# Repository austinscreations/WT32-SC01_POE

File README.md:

# WT32-SC01_POE

2023-06-28:

New sheild has been designed that is more universal. the deisgn is much smaller. uses a single 1.25mm jst conenctor to connect to the wt32-sc01 PLUS display.
adapter has been built for the WT32-S3-86s (replaces the 86v) 4" display. adapter in the works to support the orginal display as well

2022-06-23: renamed the repo as this project has evolved

There are now two shields designed for the wt32-sc01 display.
- one offers Ethernet + 802.1af POE
- second offers passive 12-24v POE + a 2.1mm jack

the thought with a passive board is that it's smaller allowing for more compact case designs to be built. and if you prefer to use 802.1af POE with the 2.1mm jack you can very eaily use a standard POE injector that normally cost about $6 from aliexpress to gain such functionality. with teh apssive baord however you are limited to using wifi.

both shields also equipped with qwiic connector for easy i2c support

designed for the use case of using the panel for homeautomation, code and gui in progress.

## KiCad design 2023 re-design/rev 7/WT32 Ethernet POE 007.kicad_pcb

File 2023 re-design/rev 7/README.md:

latest version of the WT32 Ethernet POE
works directly on the WT32-SC01 Plus, and adapters will be availble for the orginal Wt32 screen and the square 86s/86v screen

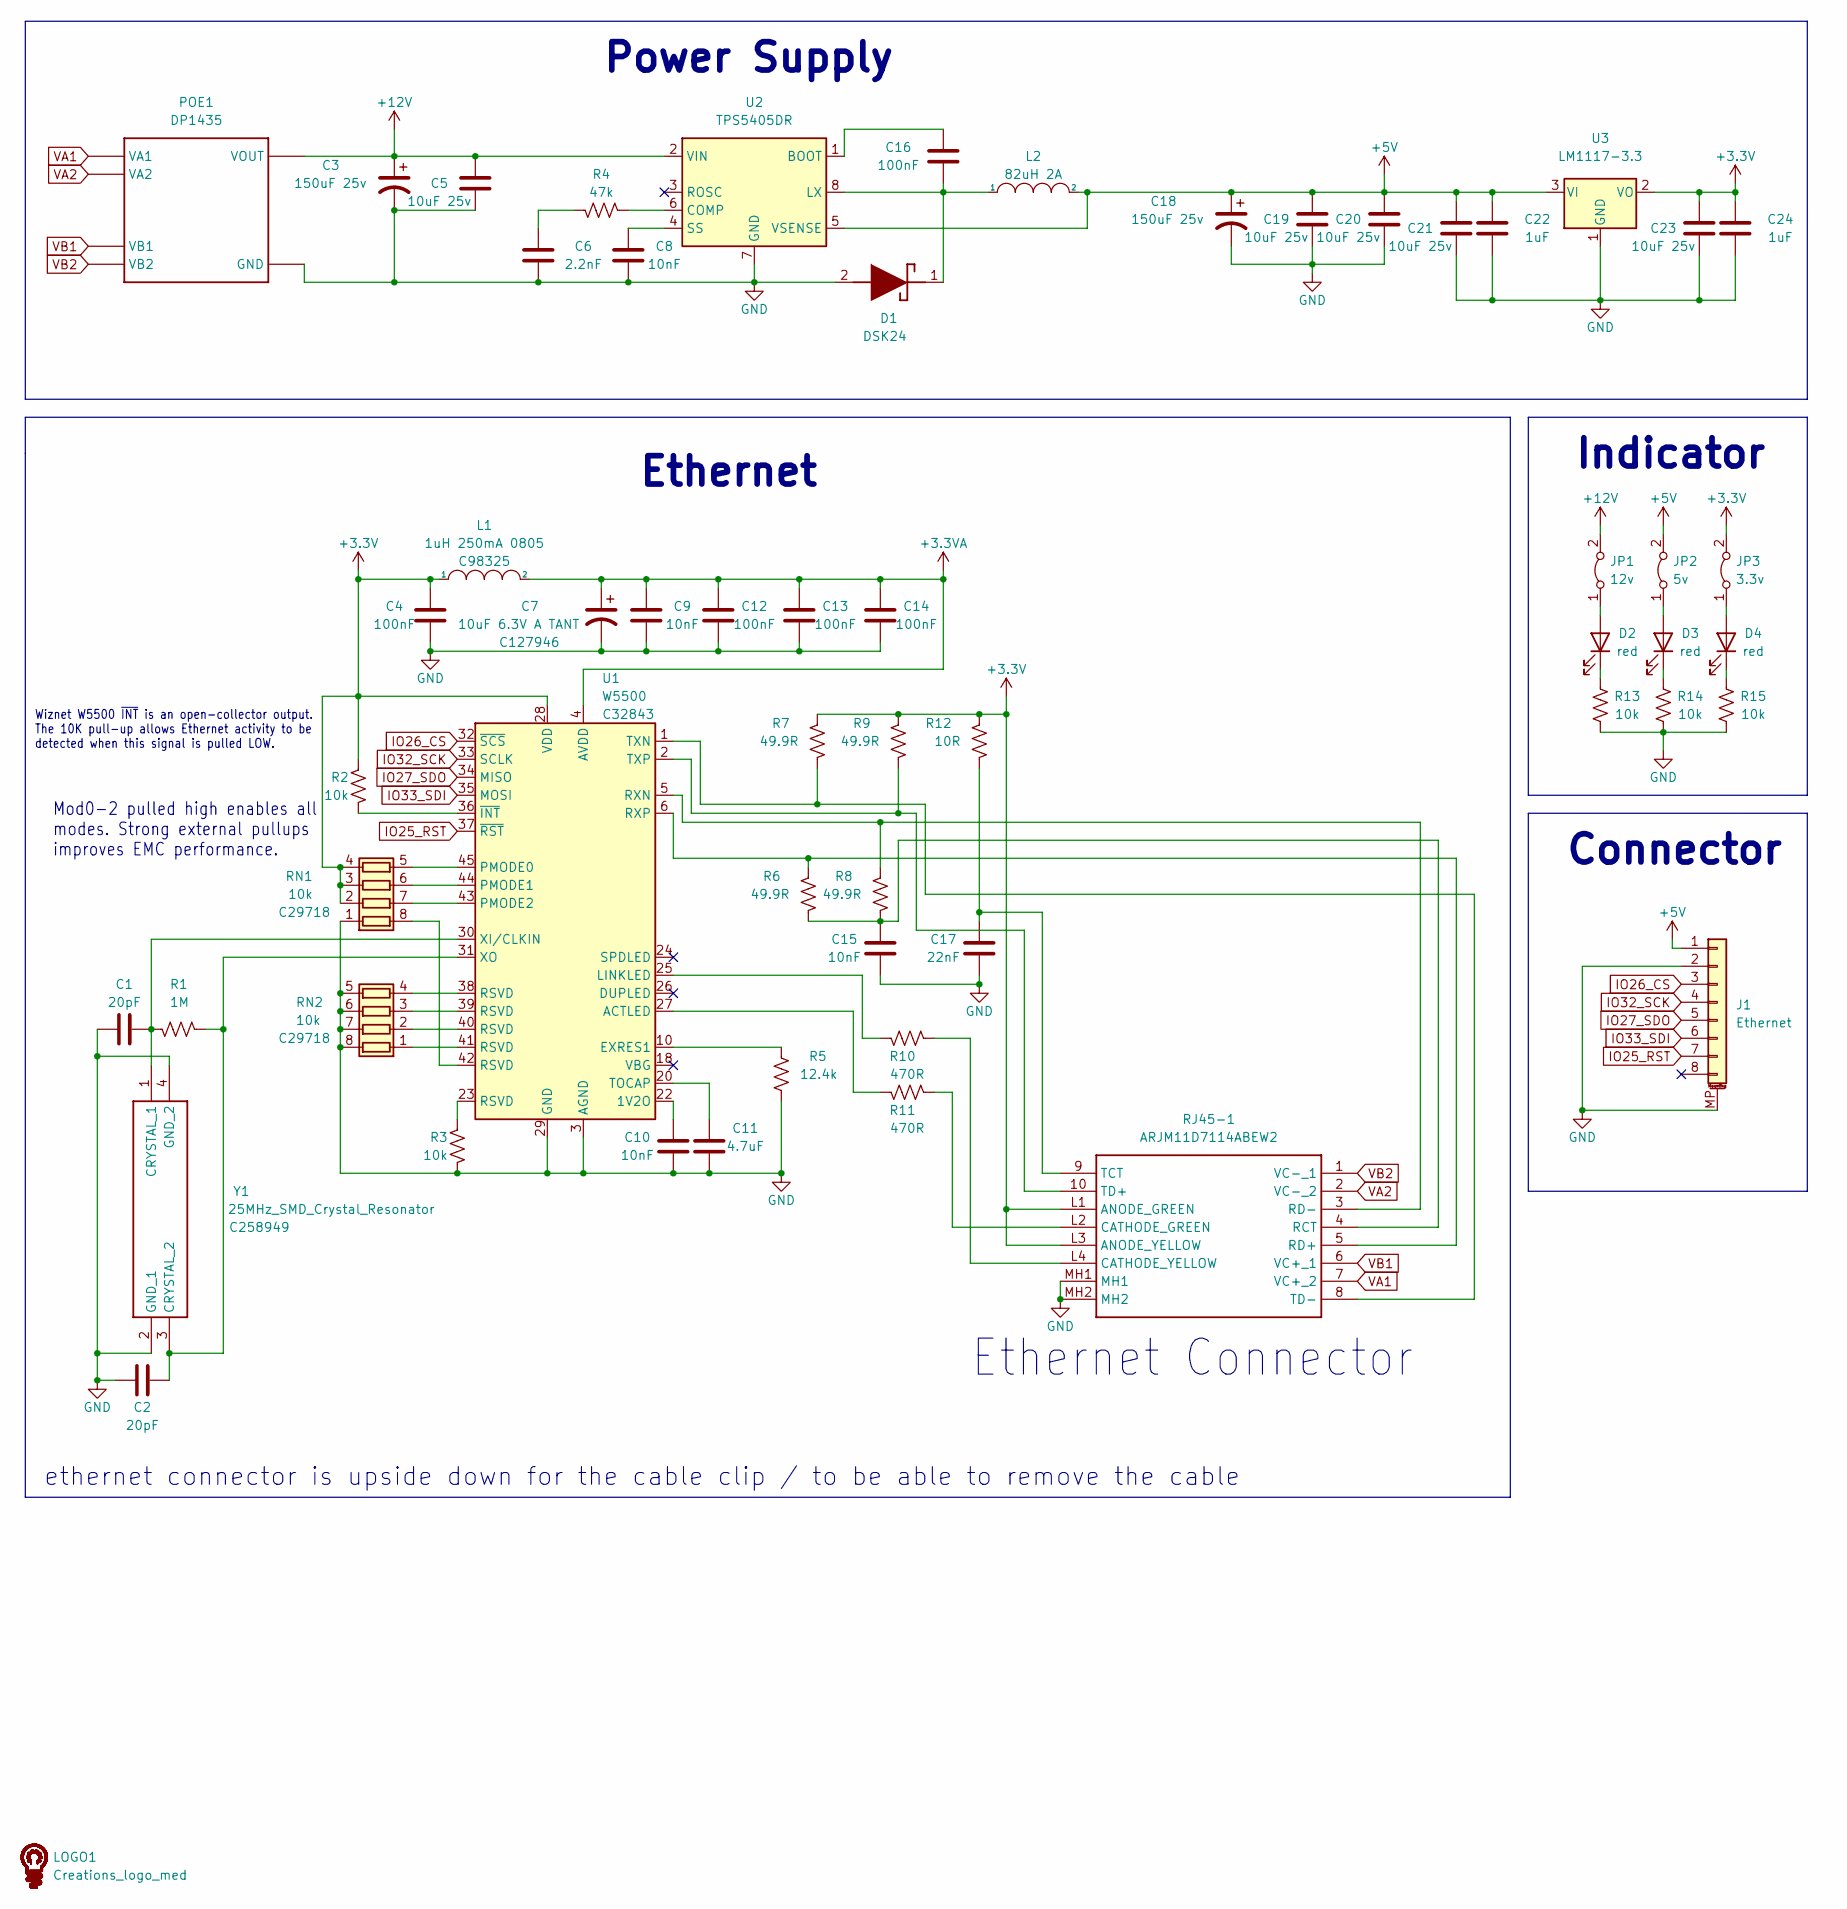
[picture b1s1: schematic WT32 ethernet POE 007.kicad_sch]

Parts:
C1, C2: 20pF; C_0603_1608Metric; LCSC C1648
C3, C18: 150uF 25v; CP_Elec_6.3x7.7; LCSC C494825
C4, C12, C13, C14, C16: 100nF; C_0603_1608Metric; LCSC C14663
C5, C19, C20, C21, C23: 10uF 25v; C_0603_1608Metric; LCSC C96446
C6: 2.2nF; C_0603_1608Metric; LCSC C1604
C7: 10uF 6.3V A TANT; CP_EIA-3216-18_Kemet-A; LCSC C127946
C8, C9, C10, C15: 10nF; C_0603_1608Metric; LCSC C57112
C11: 4.7uF; C_0603_1608Metric; LCSC C19666
C17: 22nF; C_0603_1608Metric; LCSC C21122
C22, C24: 1uF; C_0603_1608Metric; LCSC C15849
D1: DSK24; D_SOD-123; LCSC C908229
D2, D3, D4: red; LED_0603_1608Metric; LCSC C72038
J1: Ethernet; 8 pin jst 1.25 vertical; LCSC C225110
JP1: 12v; SolderJumper-2_P1.3mm_Bridged_RoundedPad1.0x1.5mm
JP2: 5v; SolderJumper-2_P1.3mm_Bridged_RoundedPad1.0x1.5mm
JP3: 3.3v; SolderJumper-2_P1.3mm_Bridged_RoundedPad1.0x1.5mm
L1: 1uH 250mA 0805; L_0805_2012Metric; LCSC C98325
L2: 82uH 2A; IND-SMD_L7.1-W6.6; LCSC C2983095
LOGO1: Creations_logo_med; Creations logo med
POE1: DP1435
R1: 1M; R_0603_1608Metric; LCSC C22935
R2, R3, R13, R14, R15: 10k; R_0603_1608Metric; LCSC C25804
R4: 47k; R_0603_1608Metric; LCSC C25819
R5: 12.4k; R_0603_1608Metric; LCSC C310267
R6, R7, R8, R9: 49.9R; R_0603_1608Metric; LCSC C23185
R10, R11: 470R; R_0603_1608Metric; LCSC C23179
R12: 10R; R_0603_1608Metric; LCSC C22859
RJ45-1: ARJM11D7114ABEW2
RN1, RN2: 10k; R_Array_Convex_4x0603; LCSC C29718
U1: W5500; LQFP-48_7x7mm_P0.5mm; LCSC C32843
U2: TPS5405DR; SOIC-8_3.9x4.9mm_P1.27mm; LCSC C488409
U3: LM1117-3.3; SOT-89-3; LCSC C126019
Y1: 25MHz_SMD_Crystal_Resonator; LCSC C258949

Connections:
+3.3V: C4.2, C23.2, C24.1, JP3.2 (B), L1.1, R2.2, R7.2, R9.2, R12.2, RJ45-1.L1 (ANODE_GREEN), RJ45-1.L3 (ANODE_YELLOW), RN1.2 (R2.1), RN1.3 (R3.1), RN1.4 (R4.1), U1.28 (VDD), U3.2 (VO)
+3.3VA: C7.1, C9.2, C12.2, C13.2, C14.2, L1.2, U1.4 (AVDD), U1.8 (AVDD), U1.11 (AVDD), U1.15 (AVDD), U1.17 (AVDD), U1.21 (AVDD)
+5V: C18.1, C19.2, C20.2, C21.2, C22.1, J1.1, JP2.2 (B), L2.2, U2.5 (VSENSE), U3.3 (VI)
+12V: C3.1, C5.2, JP1.2 (B), POE1.VOUT, U2.2 (VIN)
GND: C1.1, C2.1, C3.2, C4.1, C5.1, C6.1, C7.2, C8.1, C9.1, C10.1, C11.1, C12.1, C13.1, C14.1, C15.1, C17.1, C18.2, C19.1, C20.1, C21.1, C22.2, C23.1, C24.2, D1.2 (A), J1.2, J1.MP (MountPin), POE1.GND, R3.1, R5.1, R13.2, R14.1, R15.1, RJ45-1.MH1, RJ45-1.MH2, RN1.1 (R1.1), RN2.5 (R4.2), RN2.6 (R3.2), RN2.7 (R2.2), RN2.8 (R1.2), U1.3 (AGND), U1.9 (AGND), U1.14 (AGND), U1.16 (AGND), U1.19 (AGND), U1.29 (GND), U1.48 (AGND), U2.7 (GND), U3.1 (GND), Y1.2 (GND_1), Y1.4 (GND_2)
IO25_RST: J1.7, U1.37 (~RST)
IO26_CS: J1.3, U1.32 (~SCS)
IO27_SDO: J1.5, U1.34 (MISO)
IO32_SCK: J1.4, U1.33 (SCLK)
IO33_SDI: J1.6, U1.35 (MOSI)
unnamed: C6.2, R4.2
unnamed: C16.2, D1.1 (K), L2.1, U2.8 (LX)
unnamed: D2.2 (A), JP1.1 (A)
unnamed: D2.1 (K), R13.1
unnamed: D3.2 (A), JP2.1 (A)
unnamed: D3.1 (K), R14.2
unnamed: D4.2 (A), JP3.1 (A)
unnamed: D4.1 (K), R15.2
unnamed: R3.2, U1.23 (RSVD)
unnamed: R11.1, RJ45-1.L2 (CATHODE_GREEN)
unnamed: R10.1, RJ45-1.L4 (CATHODE_YELLOW)
unnamed: C15.2, R6.1, R8.1, RJ45-1.4 (RCT)
unnamed: R6.2, RJ45-1.5 (RD+), U1.6 (RXP)
unnamed: R8.2, RJ45-1.3 (RD-), U1.5 (RXN)
unnamed: C17.2, R12.1, RJ45-1.9 (TCT)
unnamed: R9.1, RJ45-1.10 (TD+), U1.2 (TXP)
unnamed: R7.1, RJ45-1.8 (TD-), U1.1 (TXN)
unnamed: RN1.8 (R1.2), U1.42 (RSVD)
unnamed: RN1.7 (R2.2), U1.43 (PMODE2)
unnamed: RN1.6 (R3.2), U1.44 (PMODE1)
unnamed: RN1.5 (R4.2), U1.45 (PMODE0)
unnamed: RN2.1 (R1.1), U1.41 (RSVD)
unnamed: RN2.2 (R2.1), U1.40 (RSVD)
unnamed: RN2.3 (R3.1), U1.39 (RSVD)
unnamed: RN2.4 (R4.1), U1.38 (RSVD)
unnamed: C10.2, U1.22 (1V2O)
unnamed: R11.2, U1.27 (ACTLED)
unnamed: R5.2, U1.10 (EXRES1)
unnamed: R10.2, U1.25 (LINKLED)
unnamed: C11.2, U1.20 (TOCAP)
unnamed: C1.2, R1.1, U1.30 (XI/CLKIN), Y1.1 (CRYSTAL_1)
unnamed: C2.2, R1.2, U1.31 (XO), Y1.3 (CRYSTAL_2)
unnamed: R2.1, U1.36 (~INT)
unnamed: C16.1, U2.1 (BOOT)
unnamed: R4.1, U2.6 (COMP)
unnamed: C8.2, U2.4 (SS)
VA1: POE1.VA1, RJ45-1.7 (VC+_2)
VA2: POE1.VA2, RJ45-1.2 (VC-_2)
VB1: POE1.VB1, RJ45-1.6 (VC+_1)
VB2: POE1.VB2, RJ45-1.1 (VC-_1)

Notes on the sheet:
Indicator
Power Supply
Connector
Ethernet
Ethernet Connector
ethernet connector is upside down for the cable clip / to be able to remove the cable
Wiznet W5500 ~{INT} is an open-collector output. The 10K pull-up allows Ethernet activity to be detected when this signal is pulled LOW.
Mod0-2 pulled high enables all modes. Strong external pullups improves EMC performance.

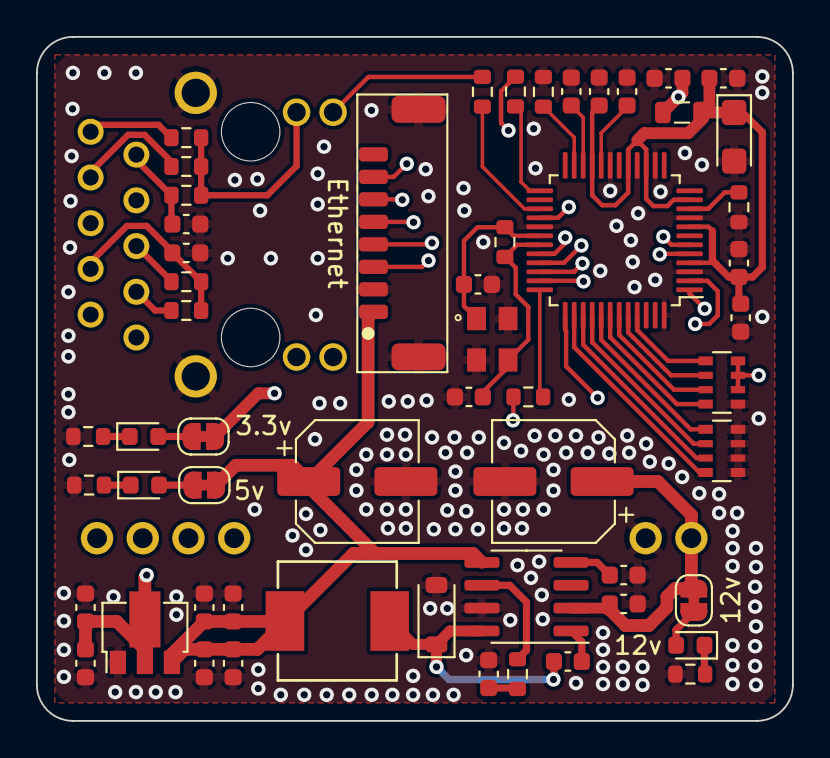
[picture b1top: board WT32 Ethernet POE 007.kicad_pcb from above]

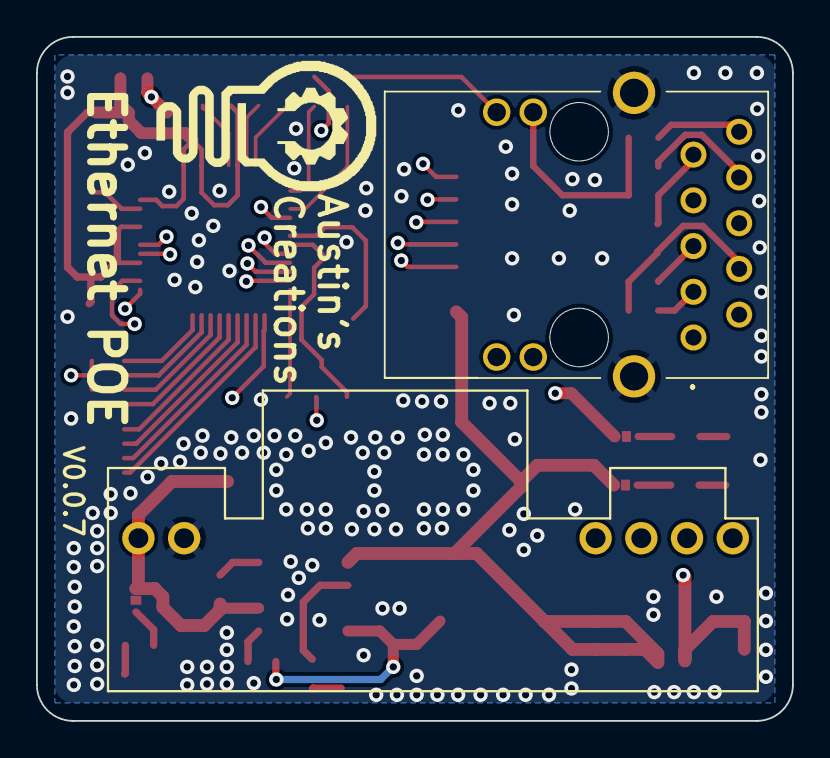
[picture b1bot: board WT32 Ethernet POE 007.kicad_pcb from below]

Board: 4 copper layers, 42.0 x 38.0 mm, 58 parts (3 on the bottom side), 50 nets.

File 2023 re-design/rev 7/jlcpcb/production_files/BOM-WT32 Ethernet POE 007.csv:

Comment,Designator,Footprint,LCSC
LM1117-3.3,U3,SOT-89-3,C126019
10uF 6.3V A TANT,C7,CP_EIA-3216-18_Kemet-A,C127946
100nF,"C12,C13,C14,C16,C4",C_0603_1608Metric,C14663
1uF,"C22,C24",C_0603_1608Metric,C15849
2.2nF,C6,C_0603_1608Metric,C1604
20pF,"C1,C2",C_0603_1608Metric,C1648
4.7uF,C11,C_0603_1608Metric,C19666
22nF,C17,C_0603_1608Metric,C21122
Ethernet,J1,8 pin jst 1.25 vertical,C225110
10R,R12,R_0603_1608Metric,C22859
1M,R1,R_0603_1608Metric,C22935
470R,"R10,R11",R_0603_1608Metric,C23179
49.9R,"R6,R7,R8,R9",R_0603_1608Metric,C23185
10k,"R13,R14,R15,R2,R3",R_0603_1608Metric,C25804
47k,R4,R_0603_1608Metric,C25819
25MHz_SMD_Crystal_Resonator,Y1,25MHz_SMD_Crystal_Resonator,C258949
10k,"RN1,RN2",R_Array_Convex_4x0603,C29718
82uH 2A,L2,IND-SMD_L7.1-W6.6,C2983095
12.4k,R5,R_0603_1608Metric,C310267
W5500,U1,LQFP-48_7x7mm_P0.5mm,C32843
TPS5405DR,U2,SOIC-8_3.9x4.9mm_P1.27mm,C488409
150uF 25v,"C18,C3",CP_Elec_6.3x7.7,C494825
10nF,"C10,C15,C8,C9",C_0603_1608Metric,C57112
red,"D2,D3,D4",LED_0603_1608Metric,C72038
DSK24,D1,D_SOD-123,C908229
10uF 25v,"C19,C20,C21,C23,C5",C_0603_1608Metric,C96446
1uH 250mA 0805,L1,L_0805_2012Metric,C98325

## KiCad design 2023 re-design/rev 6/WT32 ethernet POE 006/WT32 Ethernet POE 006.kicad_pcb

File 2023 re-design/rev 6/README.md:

# things to note

With the 86v panel you'd need both the POE module but also the adapter. along with doing modifications to the panel PCB to accept ethernet.
video of doing this modification here: <https://www.youtube.com/watch?v=REbtDBVKIto>

even with doing JLCPCBs PCBA you will need to add the ethernet jack - from mouser ARJM11D7-114-AB-EW2
I've been sourcing the POE from aliexpress - it has 2 pins on one end, 4 on the other. 12v output SDAPO DP1435
Then you need an 8 pin 1.25mm dual head JST connector. pinout should be the same pin 1 to pin 1 etc. i've been buying these from aliexpress in 100mmm length

Becuase part numbers and links change somewhat often i won't post any here but feel free to reach out on discord if you need help.

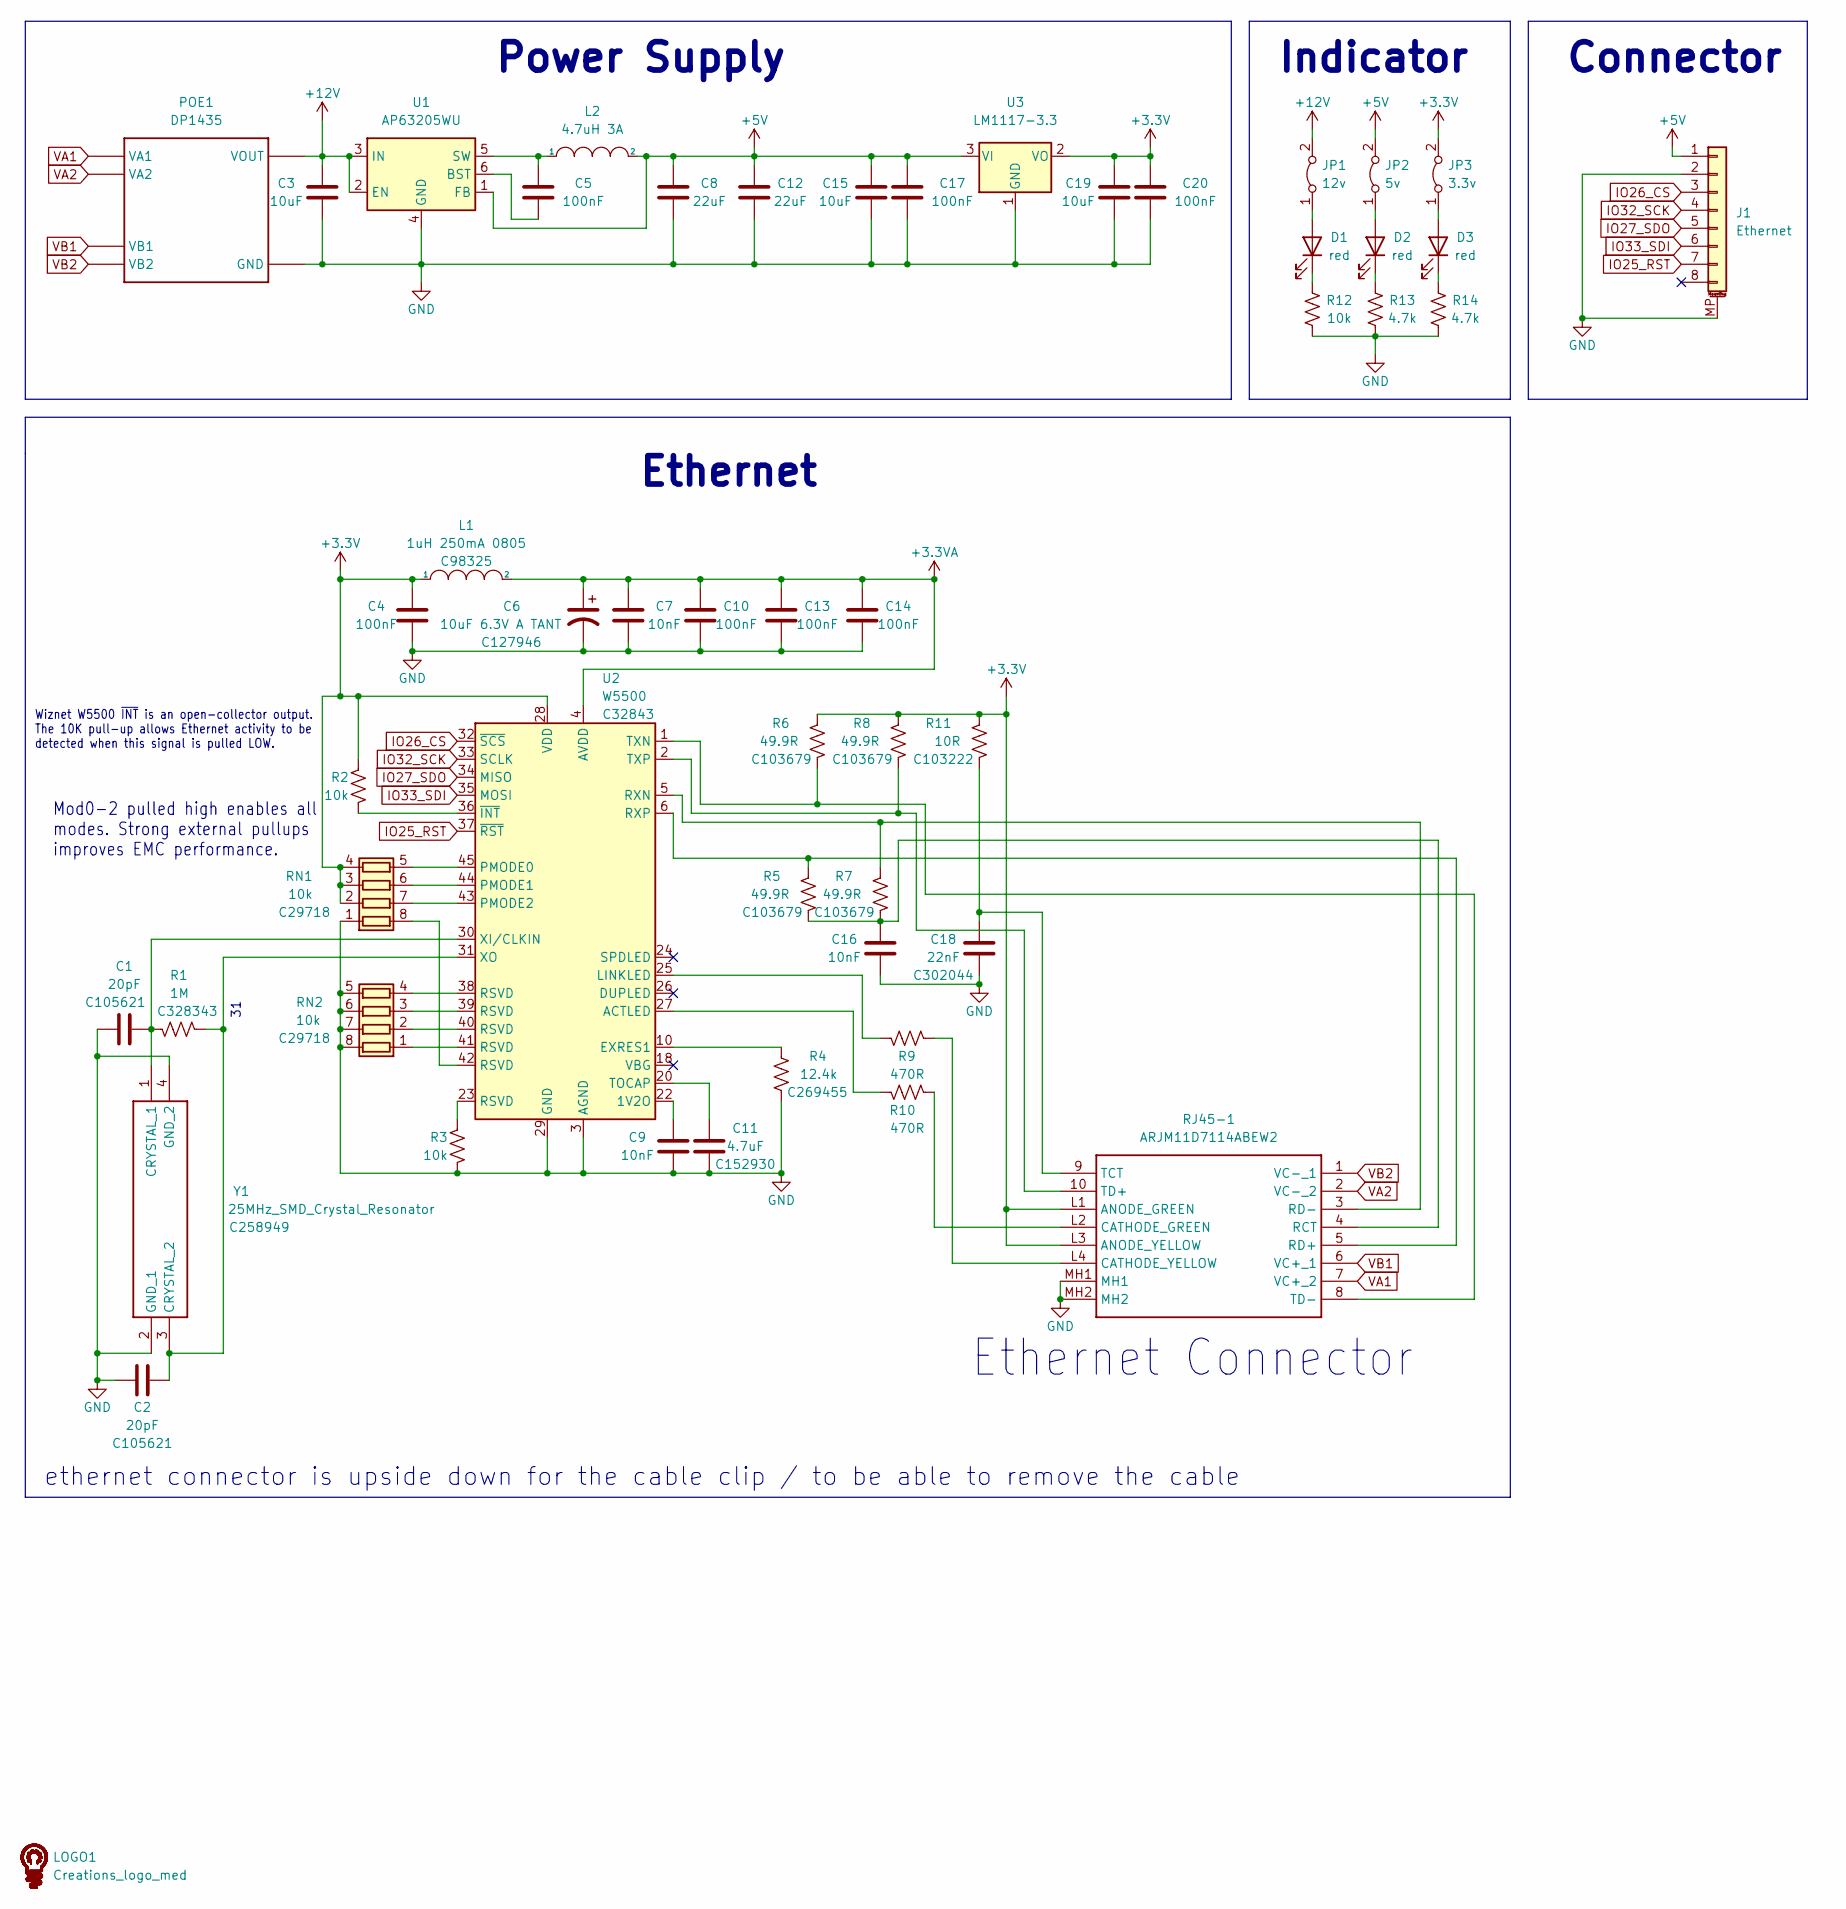
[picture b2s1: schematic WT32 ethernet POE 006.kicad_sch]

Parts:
C1, C2: 20pF; C_0603_1608Metric; LCSC C105621
C3, C15, C19: 10uF; C_0603_1608Metric; LCSC C19702
C4, C10, C13, C14: 100nF; C_0603_1608Metric; LCSC C14663
C5, C17, C20: 100nF; C_0603_1608Metric; LCSC C15849
C6: 10uF 6.3V A TANT; CP_EIA-3216-18_Kemet-A; LCSC C127946
C7, C9, C16: 10nF; C_0603_1608Metric; LCSC C57112
C8, C12: 22uF; C_0603_1608Metric; LCSC C19702
C11: 4.7uF; C_0603_1608Metric; LCSC C152930
C18: 22nF; C_0603_1608Metric; LCSC C302044
D1, D2, D3: red; LED_0603_1608Metric; LCSC C72038
J1: Ethernet; 8 pin jst 1.25 vertical; LCSC C225110
JP1: 12v; SolderJumper-2_P1.3mm_Bridged_RoundedPad1.0x1.5mm
JP2: 5v; SolderJumper-2_P1.3mm_Bridged_RoundedPad1.0x1.5mm
JP3: 3.3v; SolderJumper-2_P1.3mm_Bridged_RoundedPad1.0x1.5mm
L1: 1uH 250mA 0805; L_0805_2012Metric; LCSC C98325
L2: 4.7uH 3A; L_Sunlord_SWPA5040S; LCSC C2044594
LOGO1: Creations_logo_med; Creations logo med
POE1: DP1435
R1: 1M; R_0603_1608Metric; LCSC C328343
R2, R3: 10k; R_0603_1608Metric; LCSC C103199
R4: 12.4k; R_0603_1608Metric; LCSC C269455
R5, R6, R7, R8: 49.9R; R_0603_1608Metric; LCSC C103679
R9, R10: 470R; R_0603_1608Metric; LCSC C25241
R11: 10R; R_0603_1608Metric; LCSC C103222
R12: 10k; R_0603_1608Metric; LCSC C98220
R13, R14: 4.7k; R_0603_1608Metric; LCSC C23162
RJ45-1: ARJM11D7114ABEW2
RN1, RN2: 10k; R_Array_Convex_4x0603; LCSC C29718
U1: AP63205WU; TSOT-23-6; LCSC C2071056
U2: W5500; LQFP-48_7x7mm_P0.5mm; LCSC C32843
U3: LM1117-3.3; SOT-89-3; LCSC C126019
Y1: 25MHz_SMD_Crystal_Resonator; LCSC C258949

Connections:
+3.3V: C4.2, C19.2, C20.1, JP3.2 (B), L1.1, R2.2, R6.2, R8.2, R11.2, RJ45-1.L1 (ANODE_GREEN), RJ45-1.L3 (ANODE_YELLOW), RN1.2 (R2.1), RN1.3 (R3.1), RN1.4 (R4.1), U2.28 (VDD), U3.2 (VO)
+3.3VA: C6.1, C7.2, C10.2, C13.2, C14.2, L1.2, U2.4 (AVDD), U2.8 (AVDD), U2.11 (AVDD), U2.15 (AVDD), U2.17 (AVDD), U2.21 (AVDD)
+5V: C8.2, C12.2, C15.2, C17.1, J1.1, JP2.2 (B), L2.2, U1.1 (FB), U3.3 (VI)
+12V: C3.2, JP1.2 (B), POE1.VOUT, U1.2 (EN), U1.3 (IN)
GND: C1.1, C2.1, C3.1, C4.1, C6.2, C7.1, C8.1, C9.1, C10.1, C11.1, C12.1, C13.1, C14.1, C15.1, C16.1, C17.2, C18.1, C19.1, C20.2, J1.2, J1.MP (MountPin), POE1.GND, R3.1, R4.1, R12.2, R13.1, R14.1, RJ45-1.MH1, RJ45-1.MH2, RN1.1 (R1.1), RN2.5 (R4.2), RN2.6 (R3.2), RN2.7 (R2.2), RN2.8 (R1.2), U1.4 (GND), U2.3 (AGND), U2.9 (AGND), U2.14 (AGND), U2.16 (AGND), U2.19 (AGND), U2.29 (GND), U2.48 (AGND), U3.1 (GND), Y1.2 (GND_1), Y1.4 (GND_2)
IO25_RST: J1.7, U2.37 (~RST)
IO26_CS: J1.3, U2.32 (~SCS)
IO27_SDO: J1.5, U2.34 (MISO)
IO32_SCK: J1.4, U2.33 (SCLK)
IO33_SDI: J1.6, U2.35 (MOSI)
unnamed: C1.2, R1.1, U2.30 (XI/CLKIN), Y1.1 (CRYSTAL_1)
unnamed: C2.2, R1.2, U2.31 (XO), Y1.3 (CRYSTAL_2)
unnamed: C5.1, L2.1, U1.5 (SW)
unnamed: C5.2, U1.6 (BST)
unnamed: C9.2, U2.22 (1V2O)
unnamed: C11.2, U2.20 (TOCAP)
unnamed: C16.2, R5.1, R7.1, RJ45-1.4 (RCT)
unnamed: C18.2, R11.1, RJ45-1.9 (TCT)
unnamed: D1.1 (K), R12.1
unnamed: D1.2 (A), JP1.1 (A)
unnamed: D2.1 (K), R13.2
unnamed: D2.2 (A), JP2.1 (A)
unnamed: D3.1 (K), R14.2
unnamed: D3.2 (A), JP3.1 (A)
unnamed: R2.1, U2.36 (~INT)
unnamed: R3.2, U2.23 (RSVD)
unnamed: R4.2, U2.10 (EXRES1)
unnamed: R5.2, RJ45-1.5 (RD+), U2.6 (RXP)
unnamed: R6.1, RJ45-1.8 (TD-), U2.1 (TXN)
unnamed: R7.2, RJ45-1.3 (RD-), U2.5 (RXN)
unnamed: R8.1, RJ45-1.10 (TD+), U2.2 (TXP)
unnamed: R9.1, RJ45-1.L4 (CATHODE_YELLOW)
unnamed: R9.2, U2.25 (LINKLED)
unnamed: R10.1, RJ45-1.L2 (CATHODE_GREEN)
unnamed: R10.2, U2.27 (ACTLED)
unnamed: RN1.5 (R4.2), U2.45 (PMODE0)
unnamed: RN1.6 (R3.2), U2.44 (PMODE1)
unnamed: RN1.7 (R2.2), U2.43 (PMODE2)
unnamed: RN1.8 (R1.2), U2.42 (RSVD)
unnamed: RN2.1 (R1.1), U2.41 (RSVD)
unnamed: RN2.2 (R2.1), U2.40 (RSVD)
unnamed: RN2.3 (R3.1), U2.39 (RSVD)
unnamed: RN2.4 (R4.1), U2.38 (RSVD)
VA1: POE1.VA1, RJ45-1.7 (VC+_2)
VA2: POE1.VA2, RJ45-1.2 (VC-_2)
VB1: POE1.VB1, RJ45-1.6 (VC+_1)
VB2: POE1.VB2, RJ45-1.1 (VC-_1)

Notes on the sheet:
Indicator
Power Supply
Connector
Ethernet
Ethernet Connector
ethernet connector is upside down for the cable clip / to be able to remove the cable
Wiznet W5500 ~{INT} is an open-collector output. The 10K pull-up allows Ethernet activity to be detected when this signal is pulled LOW.
Mod0-2 pulled high enables all modes. Strong external pullups improves EMC performance.

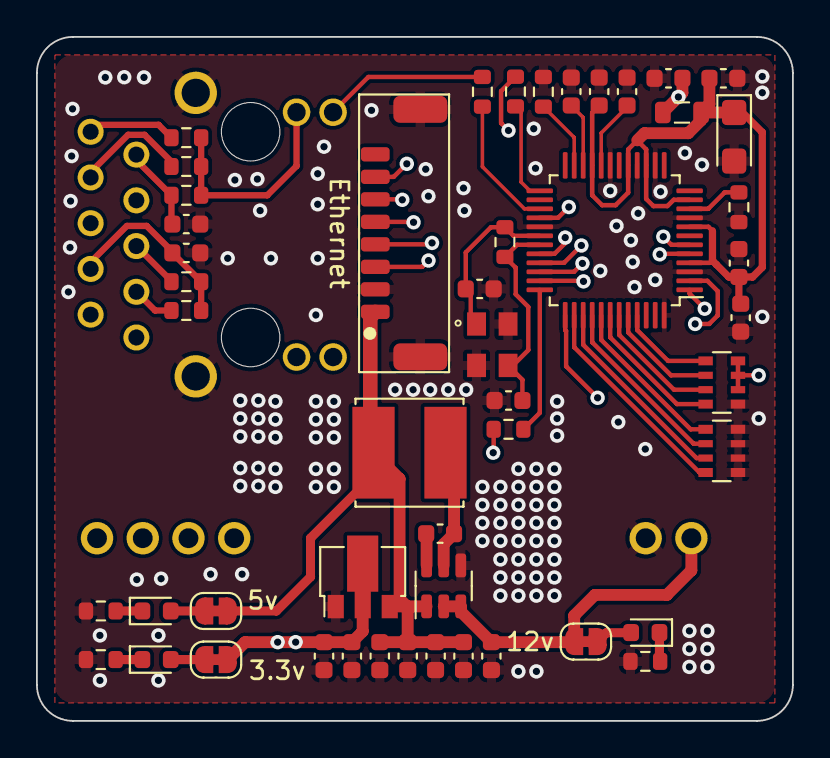
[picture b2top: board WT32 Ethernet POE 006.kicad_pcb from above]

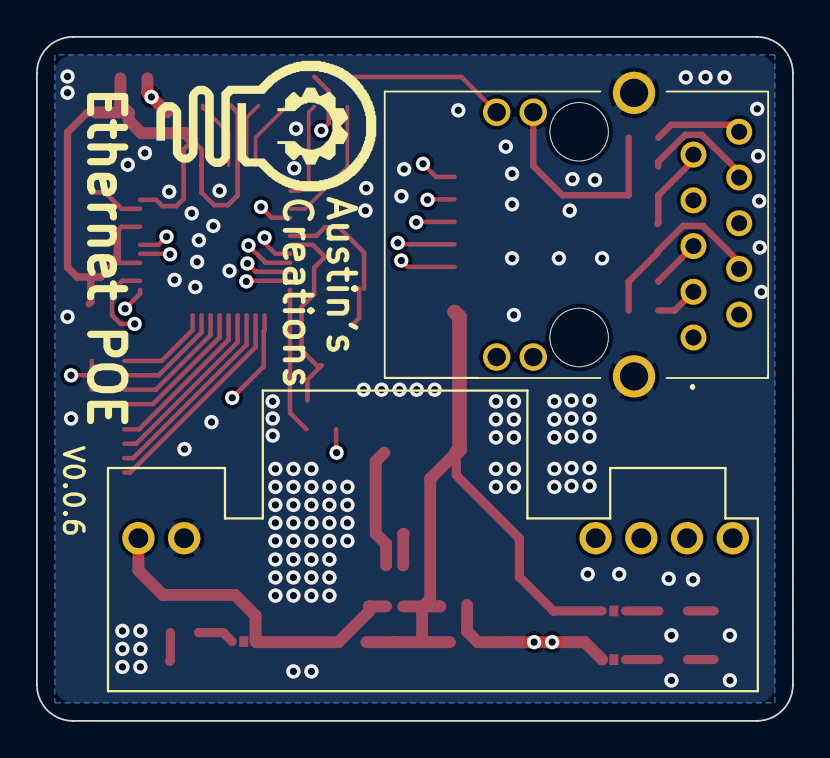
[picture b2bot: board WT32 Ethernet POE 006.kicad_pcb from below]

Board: 4 copper layers, 42.0 x 38.0 mm, 52 parts (3 on the bottom side), 47 nets.

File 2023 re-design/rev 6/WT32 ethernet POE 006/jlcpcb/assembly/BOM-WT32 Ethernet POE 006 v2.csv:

Comment+ADs-Designator+ADs-Footprint+ADs-LCSC
10k+ADs-R2,R3,R12,R13,R14+ADs-R+AF8-0603+AF8-1608Metric+ADs-C25804 
10R+ADs-R11+ADs-R+AF8-0603+AF8-1608Metric+ADs-C22859 
49.9R+ADs-R5,R6,R7,R8+ADs-R+AF8-0603+AF8-1608Metric+ADs-C23185 
20pF+ADs-C1,C2+ADs-C+AF8-0603+AF8-1608Metric+ADs-C1648
LM1117+AC0-3.3+ADs-U3+ADs-SOT+AC0-89+AC0-3+ADs-C126019
10uF 6.3V A TANT+ADs-C6+ADs-CP+AF8-EIA+AC0-3216+AC0-18+AF8-Kemet+AC0-A+ADs-C127946
100nF+ADs-C10,C13,C14,C4,C17,C20,C5+ADs-C+AF8-0603+AF8-1608Metric+ADs-C14663
4.7uF+ADs-C11+ADs-C+AF8-0603+AF8-1608Metric+ADs-C19666
22uF+ADs-C12,C15,C19,C3,C8+ADs-C+AF8-0603+AF8-1608Metric+ADs-C59461
4.7uH 3A+ADs-L2+ADs-L+AF8-Sunlord+AF8-SWPA5040S+ADs-C2044594
AP63205WU+ADs-U1+ADs-TSOT+AC0-23+AC0-6+ADs-C2071056
Ethernet+ADs-J1+ADs-8 pin jst 1.25 vertical+ADs-C225110
470R+ADs-R10,R9+ADs-R+AF8-0603+AF8-1608Metric+ADs-C23179
25MHz+AF8-SMD+AF8-Crystal+AF8-Resonator+ADs-Y1+ADs-25MHz+AF8-SMD+AF8-Crystal+AF8-Resonator+ADs-C258949
12.4k+ADs-R4+ADs-R+AF8-0603+AF8-1608Metric+ADs-C269455
10k+ADs-RN1,RN2+ADs-R+AF8-Array+AF8-Convex+AF8-4x0603+ADs-C29718
22nF+ADs-C18+ADs-C+AF8-0603+AF8-1608Metric+ADs-C21122
1M+ADs-R1+ADs-R+AF8-0603+AF8-1608Metric+ADs-C22935
W5500+ADs-U2+ADs-LQFP+AC0-48+AF8-7x7mm+AF8-P0.5mm+ADs-C32843
10nF+ADs-C16,C7,C9+ADs-C+AF8-0603+AF8-1608Metric+ADs-C57112
red+ADs-D1,D2,D3+ADs-LED+AF8-0603+AF8-1608Metric+ADs-C72038
1uH 250mA 0805+ADs-L1+ADs-L+AF8-0805+AF8-2012Metric+ADs-C98325

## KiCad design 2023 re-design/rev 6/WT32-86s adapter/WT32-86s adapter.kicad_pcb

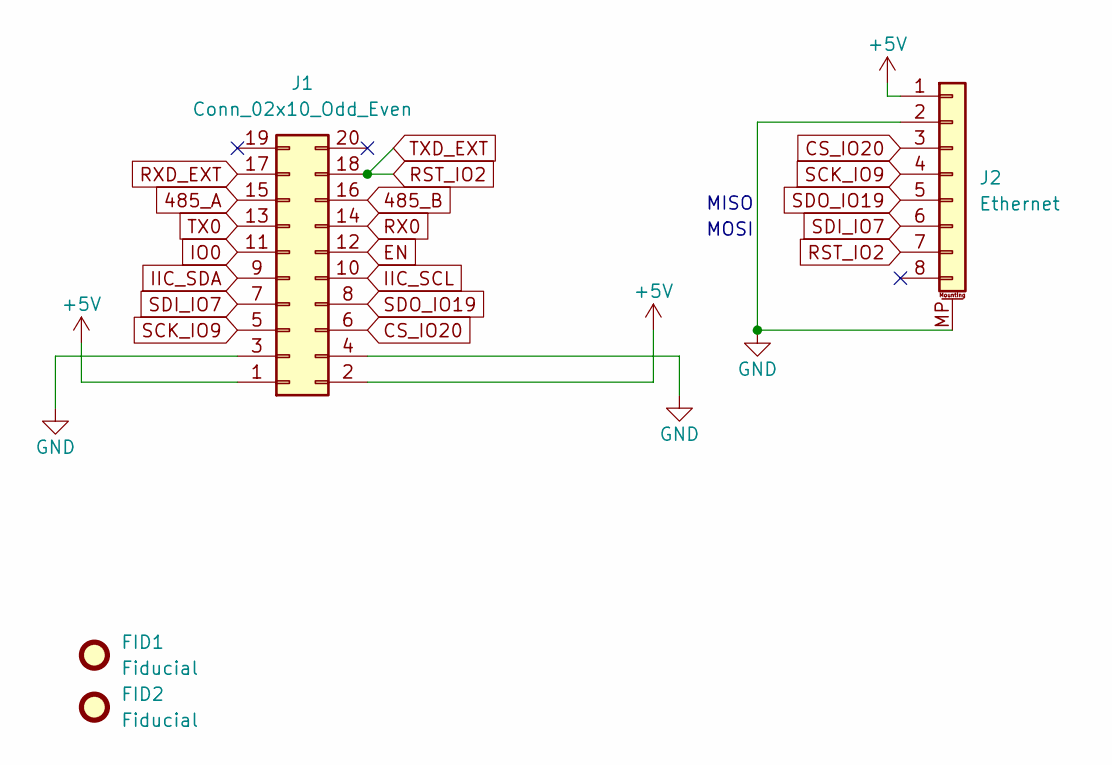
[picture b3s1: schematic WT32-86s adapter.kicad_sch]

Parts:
FID1, FID2: Fiducial; Fiducial_1mm_Mask2mm
J1: Conn_02x10_Odd_Even; PinHeader_2x10_P2.00mm_Vertical; LCSC C2935965
J2: Ethernet; JST_GH_SM08B-GHS-TB_1x08-1MP_P1.25mm_Horizontal; LCSC C225117

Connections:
485_A: J1.15
485_B: J1.16
+5V: J1.1, J1.2, J2.1
CS_IO20: J1.6, J2.3
EN: J1.12
GND: J1.3, J1.4, J2.2, J2.MP (MountPin)
IIC_SCL: J1.10
IIC_SDA: J1.9
IO0: J1.11
RX0: J1.14
RXD_EXT: J1.17
SCK_IO9: J1.5, J2.4
SDI_IO7: J1.7, J2.6
SDO_IO19: J1.8, J2.5
TX0: J1.13
TXD_EXT: J1.18, J2.7

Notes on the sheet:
MOSI
MISO

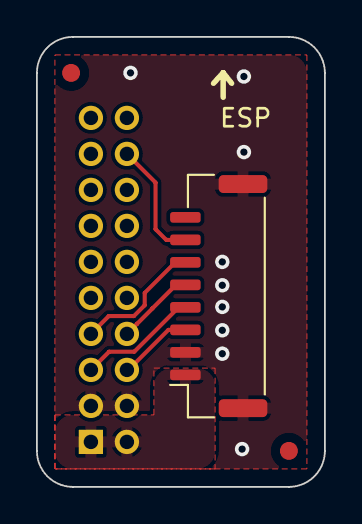
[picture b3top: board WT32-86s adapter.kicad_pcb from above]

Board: 2 copper layers, 16.0 x 25.0 mm, 4 parts (1 on the bottom side), 7 nets.

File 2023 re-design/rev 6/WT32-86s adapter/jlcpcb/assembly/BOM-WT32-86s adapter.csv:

Comment,Designator,Footprint,LCSC
Ethernet,J2,JST_GH_SM08B-GHS-TB_1x08-1MP_P1.25mm_Horizontal,C225117
Conn_02x10_Odd_Even,J1,PinHeader_2x10_P2.00mm_Vertical,C2935965

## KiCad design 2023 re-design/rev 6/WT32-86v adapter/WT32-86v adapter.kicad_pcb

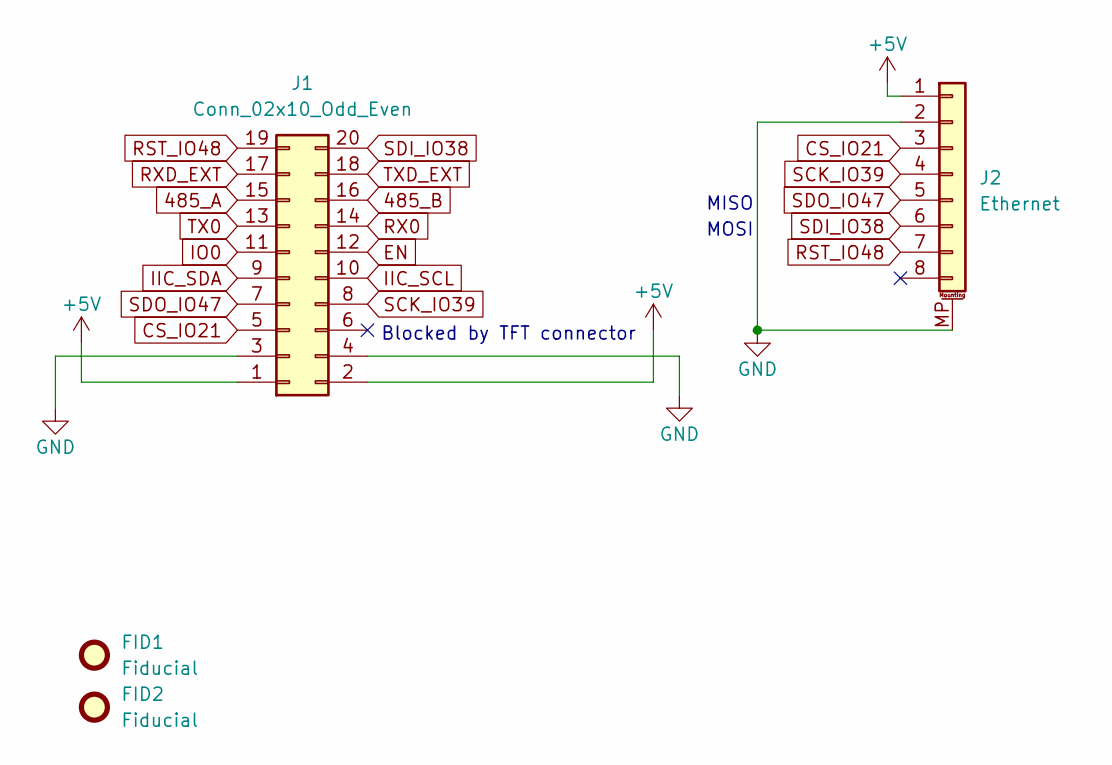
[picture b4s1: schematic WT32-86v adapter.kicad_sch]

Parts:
FID1, FID2: Fiducial; Fiducial_1mm_Mask2mm
J1: Conn_02x10_Odd_Even; PinHeader_2x10_P2.00mm_Vertical; LCSC C2935965
J2: Ethernet; JST_GH_SM08B-GHS-TB_1x08-1MP_P1.25mm_Horizontal; LCSC C225117

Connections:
485_A: J1.15
485_B: J1.16
+5V: J1.1, J1.2, J2.1
CS_IO21: J1.5, J2.3
EN: J1.12
GND: J1.3, J1.4, J2.2, J2.MP (MountPin)
IIC_SCL: J1.10
IIC_SDA: J1.9
IO0: J1.11
RST_IO48: J1.19, J2.7
RX0: J1.14
RXD_EXT: J1.17
SCK_IO39: J1.8, J2.4
SDI_IO38: J1.20, J2.6
SDO_IO47: J1.7, J2.5
TX0: J1.13
TXD_EXT: J1.18

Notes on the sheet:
Blocked by TFT connector
MOSI
MISO

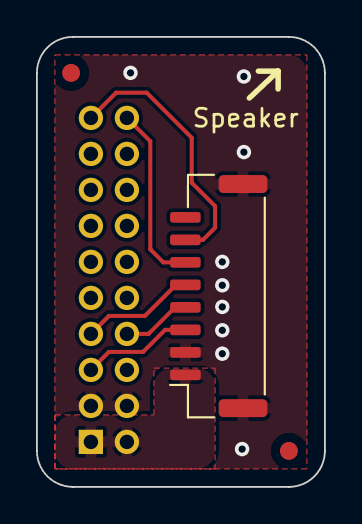
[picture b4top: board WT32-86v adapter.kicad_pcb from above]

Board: 2 copper layers, 16.0 x 25.0 mm, 4 parts (1 on the bottom side), 7 nets.

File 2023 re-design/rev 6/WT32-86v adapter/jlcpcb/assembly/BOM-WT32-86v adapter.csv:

Comment,Designator,Footprint,LCSC
Ethernet,J2,JST_GH_SM08B-GHS-TB_1x08-1MP_P1.25mm_Horizontal,C225110
Conn_02x10_Odd_Even,J1,PinHeader_2x10_P2.00mm_Vertical,C2935965
